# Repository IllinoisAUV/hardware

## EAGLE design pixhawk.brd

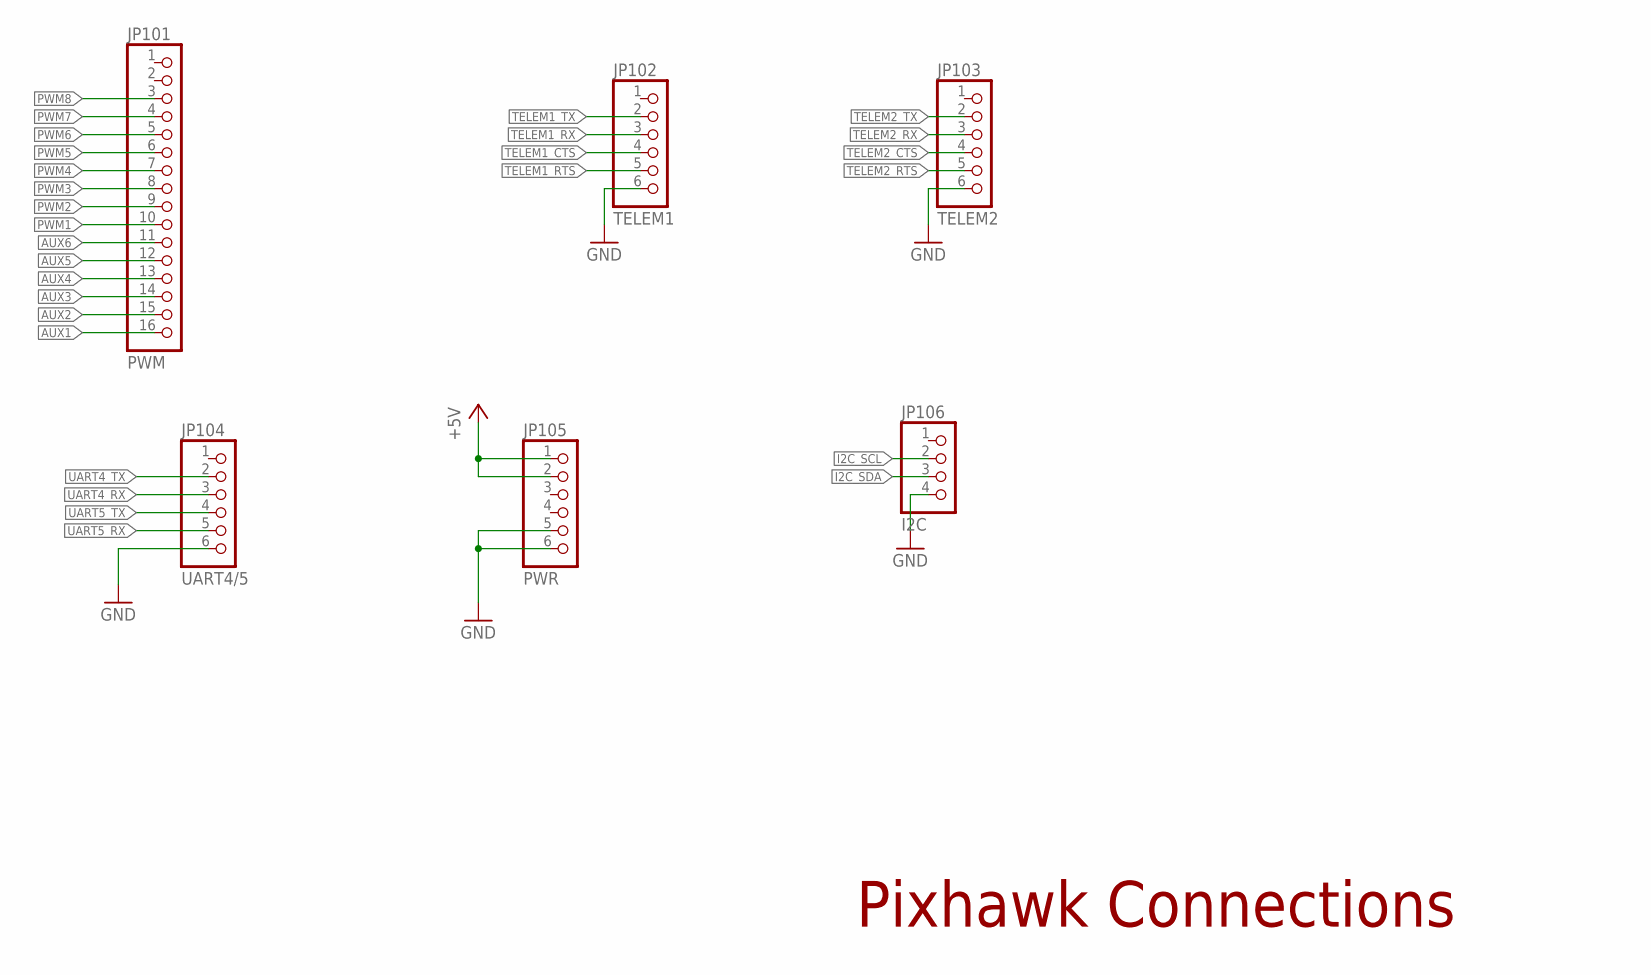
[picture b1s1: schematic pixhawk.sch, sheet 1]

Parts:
JP101: PWM; 1X16
JP102: TELEM1; 1X06
JP103: TELEM2; 1X06
JP104: UART4/5; 1X06
JP105: PWR; 1X06
JP106: I2C; 1X04

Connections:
+5V: JP105.1, JP105.2; also elsewhere on the board
AUX1: JP101.16; also elsewhere on the board
AUX2: JP101.15; also elsewhere on the board
AUX3: JP101.14; also elsewhere on the board
AUX4: JP101.13; also elsewhere on the board
AUX5: JP101.12; also elsewhere on the board
AUX6: JP101.11; also elsewhere on the board
GND: JP102.6, JP103.6, JP104.6, JP105.5, JP105.6, JP106.4; also elsewhere on the board
I2C_SCL: JP106.2; also elsewhere on the board
I2C_SDA: JP106.3; also elsewhere on the board
PWM1: JP101.10; also elsewhere on the board
PWM2: JP101.9; also elsewhere on the board
PWM3: JP101.8; also elsewhere on the board
PWM4: JP101.7; also elsewhere on the board
PWM5: JP101.6; also elsewhere on the board
PWM6: JP101.5; also elsewhere on the board
PWM7: JP101.4; also elsewhere on the board
PWM8: JP101.3; also elsewhere on the board
TELEM1_CTS: JP102.4
TELEM1_RTS: JP102.5
TELEM1_RX: JP102.3; also elsewhere on the board
TELEM1_TX: JP102.2; also elsewhere on the board
TELEM2_CTS: JP103.4
TELEM2_RTS: JP103.5
TELEM2_RX: JP103.3; also elsewhere on the board
TELEM2_TX: JP103.2; also elsewhere on the board
UART4_RX: JP104.3; also elsewhere on the board
UART4_TX: JP104.2; also elsewhere on the board
UART5_RX: JP104.5; also elsewhere on the board
UART5_TX: JP104.4; also elsewhere on the board

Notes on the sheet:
Pixhawk Connections

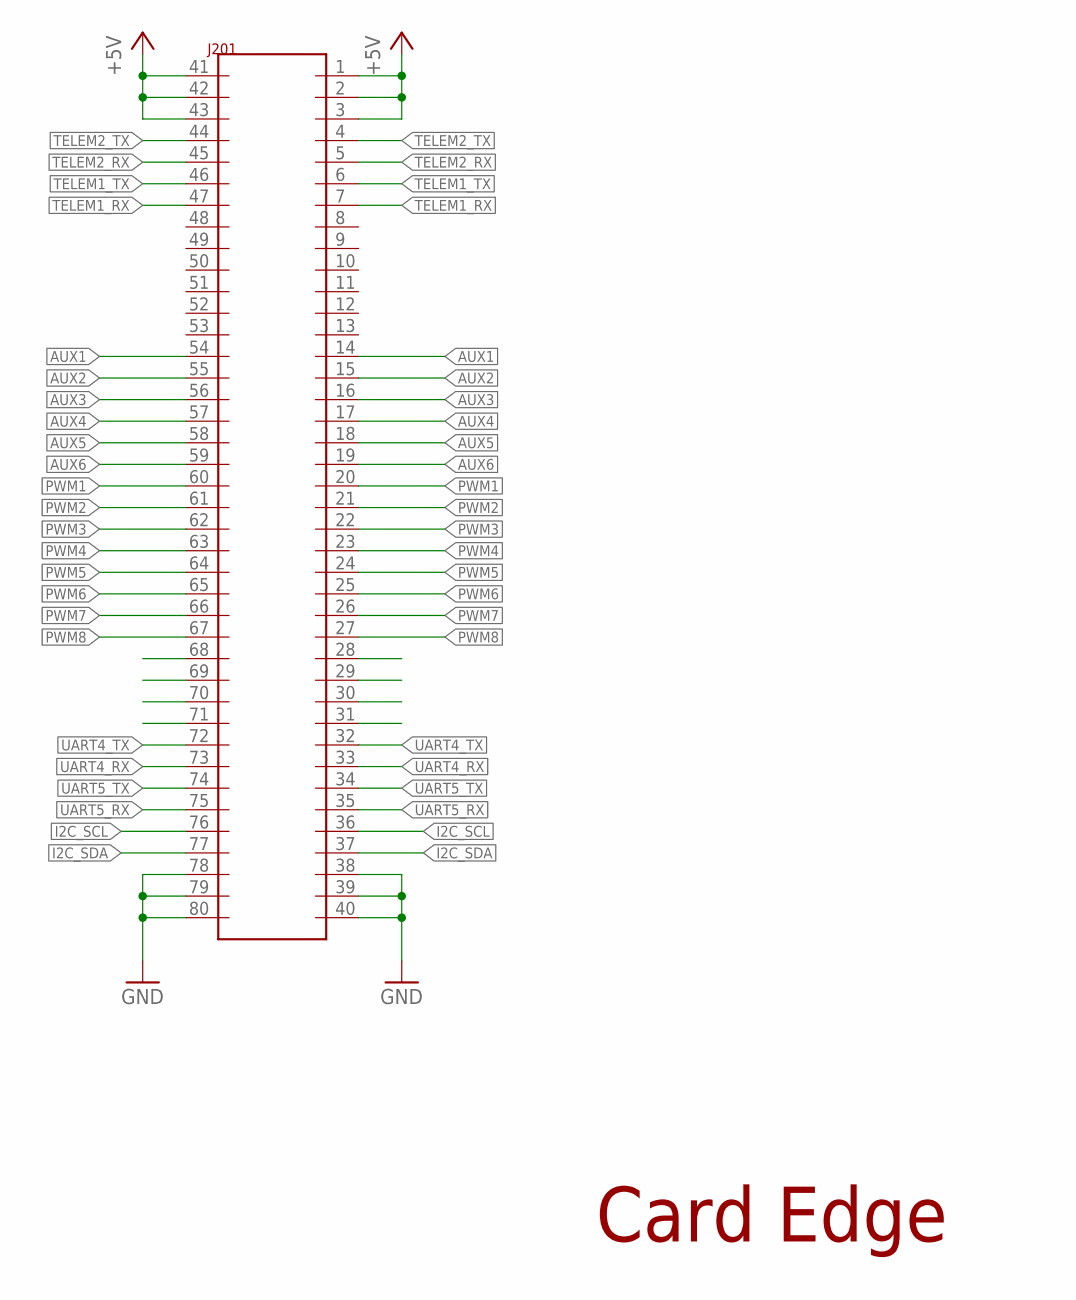
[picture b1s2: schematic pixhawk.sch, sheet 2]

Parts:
J201: 80-PIN-CARD-EDGE

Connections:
+5V: J201.1, J201.2, J201.3, J201.41, J201.42, J201.43; also elsewhere on the board
AUX1: J201.14, J201.54; also elsewhere on the board
AUX2: J201.15, J201.55; also elsewhere on the board
AUX3: J201.16, J201.56; also elsewhere on the board
AUX4: J201.17, J201.57; also elsewhere on the board
AUX5: J201.18, J201.58; also elsewhere on the board
AUX6: J201.19, J201.59; also elsewhere on the board
CAN_H: J201.30, J201.70
CAN_L: J201.31, J201.71
GND: J201.38, J201.39, J201.40, J201.78, J201.79, J201.80; also elsewhere on the board
I2C_SCL: J201.36, J201.76; also elsewhere on the board
I2C_SDA: J201.37, J201.77; also elsewhere on the board
PWM1: J201.20, J201.60; also elsewhere on the board
PWM2: J201.21, J201.61; also elsewhere on the board
PWM3: J201.22, J201.62; also elsewhere on the board
PWM4: J201.23, J201.63; also elsewhere on the board
PWM5: J201.24, J201.64; also elsewhere on the board
PWM6: J201.25, J201.65; also elsewhere on the board
PWM7: J201.26, J201.66; also elsewhere on the board
PWM8: J201.27, J201.67; also elsewhere on the board
TELEM1_RX: J201.7, J201.47; also elsewhere on the board
TELEM1_TX: J201.6, J201.46; also elsewhere on the board
TELEM2_RX: J201.5, J201.45; also elsewhere on the board
TELEM2_TX: J201.4, J201.44; also elsewhere on the board
UART4_RX: J201.33, J201.73; also elsewhere on the board
UART4_TX: J201.32, J201.72; also elsewhere on the board
UART5_RX: J201.35, J201.75; also elsewhere on the board
UART5_TX: J201.34, J201.74; also elsewhere on the board

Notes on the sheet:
Card Edge

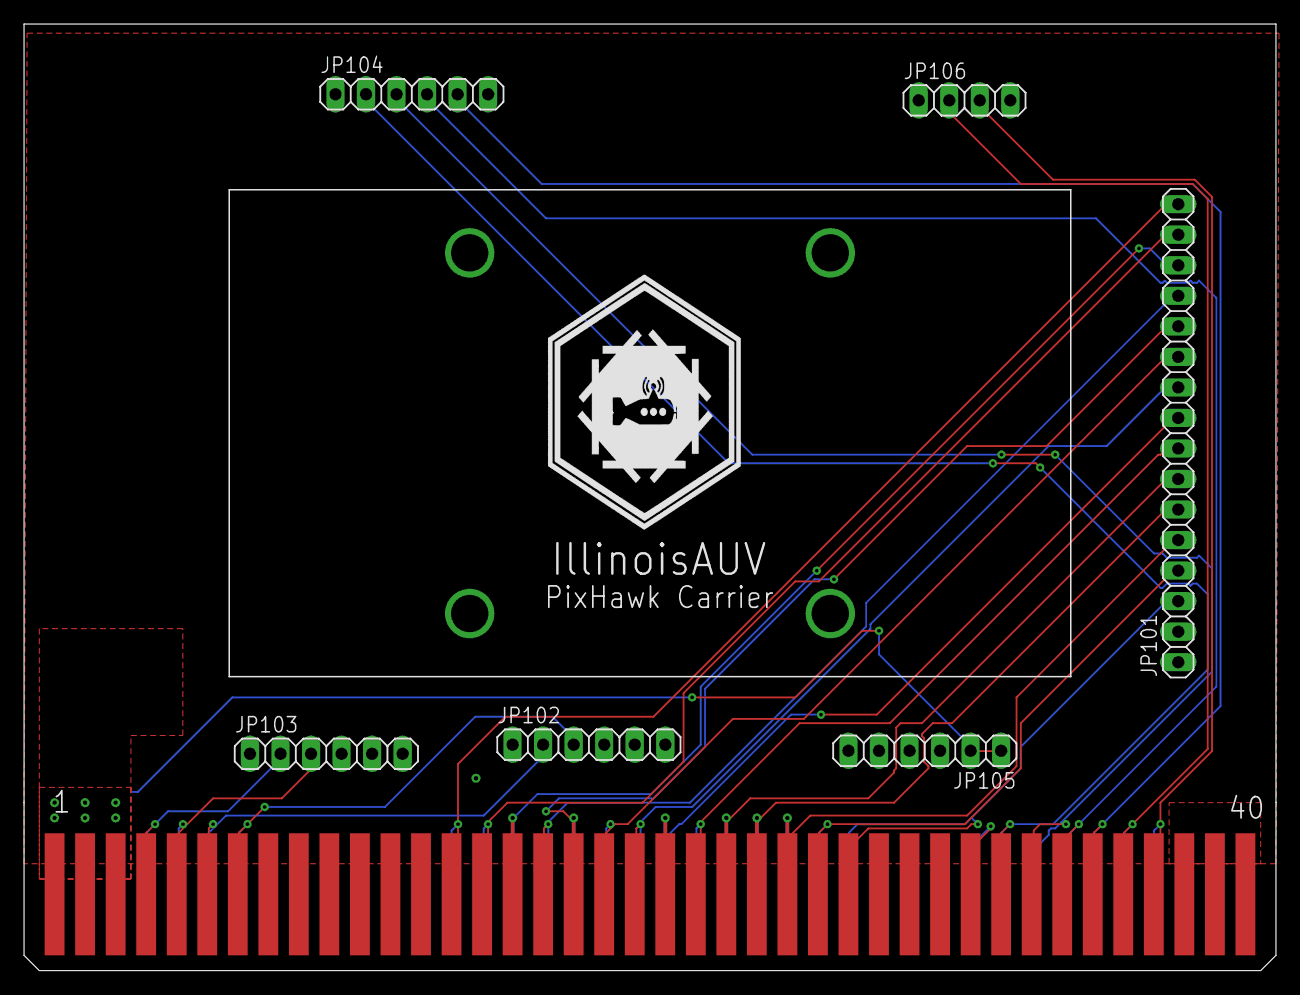
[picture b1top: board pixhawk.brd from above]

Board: 2 copper layers, 104.1 x 78.7 mm, 9 parts (0 on the bottom side), 28 nets.

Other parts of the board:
U$1: PIXHAWK_MOUNTING_HOLES
U$2: ILLINOISAUV

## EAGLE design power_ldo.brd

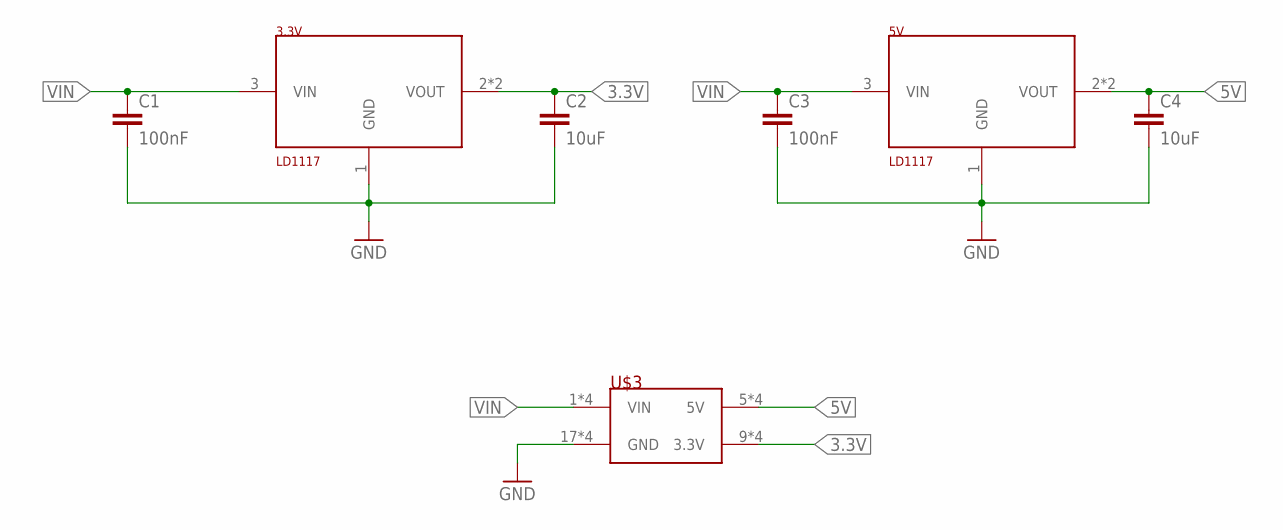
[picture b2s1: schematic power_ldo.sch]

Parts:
3.3V, 5V: LD1117"; SOT223
C1, C3: 100nF; C0603
C2, C4: 10uF; C0603
U$3: POWER_EDGE_CONNEDGE; 20-PIN-CARD-EDGE

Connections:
3.3V: 3.3V.2 (VOUT), 3.3V.4 (VOUT), C2.1, U$3.9 (3.3V), U$3.10 (3.3V), U$3.11 (3.3V), U$3.12 (3.3V)
5V: 5V.2 (VOUT), 5V.4 (VOUT), C4.1, U$3.5 (5V), U$3.6 (5V), U$3.7 (5V), U$3.8 (5V)
GND: 3.3V.1 (GND), 5V.1 (GND), C1.2, C2.2, C3.2, C4.2, U$3.17 (GND), U$3.18 (GND), U$3.19 (GND), U$3.20 (GND)
VIN: 3.3V.3 (VIN), 5V.3 (VIN), C1.1, C3.1, U$3.1 (VIN), U$3.2 (VIN), U$3.3 (VIN), U$3.4 (VIN)

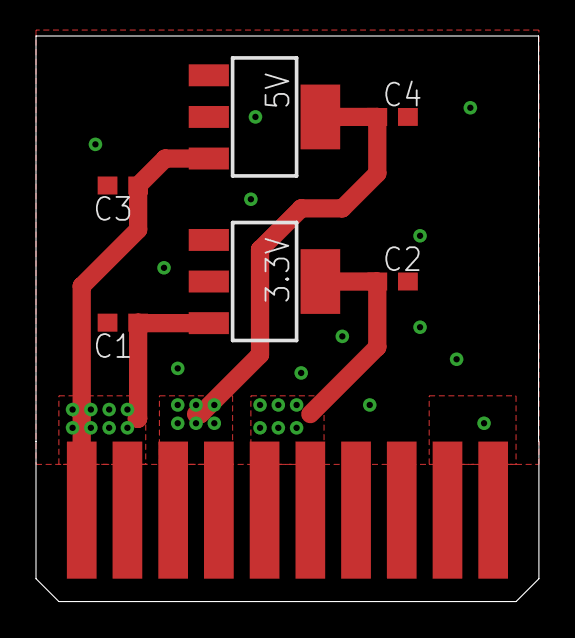
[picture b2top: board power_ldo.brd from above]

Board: 2 copper layers, 27.9 x 31.4 mm, 8 parts (1 on the bottom side), 4 nets.

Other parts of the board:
U$1: ILLINOISAUV

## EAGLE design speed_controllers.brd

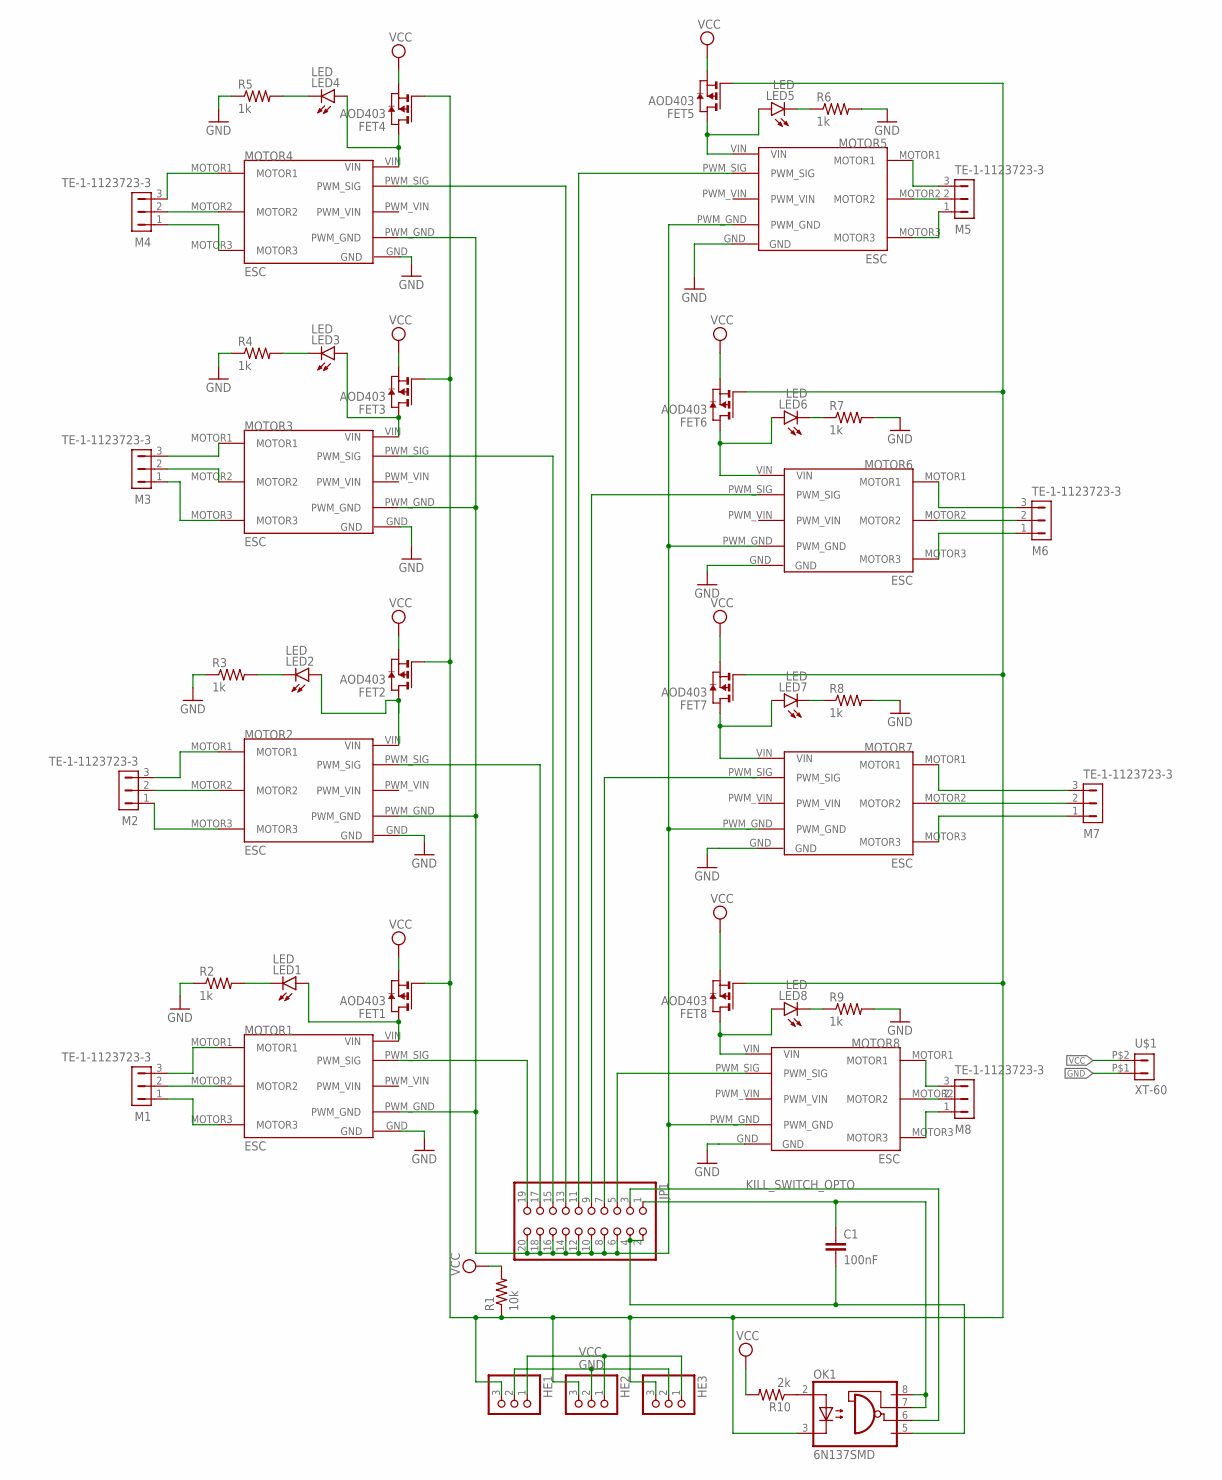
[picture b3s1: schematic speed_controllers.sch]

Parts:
C1: 100nF; C0603
FET1, FET2, FET3, FET4, FET5, FET6, FET7, FET8: AOD403; TO252
HE1, HE2, HE3: PINHD-1X3; 1X03
JP1: PINHD-2X10; 2X10
LED1, LED2, LED3, LED4, LED5, LED6, LED7, LED8: LED; LED-0603
M1, M2, M3, M4, M5, M6, M7, M8: TE-1-1123723-3
MOTOR1, MOTOR2, MOTOR3, MOTOR4, MOTOR5, MOTOR6, MOTOR7, MOTOR8: ESC
OK1: 6N137SMD; DIL8-SMD
R1: 10k; R0603
R2, R3, R4, R5, R6, R7, R8, R9: 1k; R0603
R10: 2k; R0603
U$1: XT-60

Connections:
FET_G: FET1.G, FET2.G, FET3.G, FET4.G, FET5.G, FET6.G, FET7.G, FET8.G, HE1.3, HE2.3, HE3.3, OK1.3 (C), R1.1
GND: HE1.2, HE2.2, HE3.2, MOTOR1.GND, MOTOR2.GND, MOTOR3.GND, MOTOR4.GND, MOTOR5.GND, MOTOR6.GND, MOTOR7.GND, MOTOR8.GND, R2.1, R3.1, R4.1, R5.1, R6.2, R7.2, R8.2, R9.2, U$1.P$1 (2)
KILL_SWITCH_OPTO: JP1.3, OK1.6 (VO)
M1_1: M1.1, MOTOR1.MOTOR3
M1_2: M1.2, MOTOR1.MOTOR2
M1_3: M1.3, MOTOR1.MOTOR1
M2_1: M2.1, MOTOR2.MOTOR3
M2_2: M2.2, MOTOR2.MOTOR2
M2_3: M2.3, MOTOR2.MOTOR1
M3_1: M3.1, MOTOR3.MOTOR3
M3_2: M3.2, MOTOR3.MOTOR2
M3_3: M3.3, MOTOR3.MOTOR1
M4_1: M4.1, MOTOR4.MOTOR3
M4_2: M4.2, MOTOR4.MOTOR2
M4_3: M4.3, MOTOR4.MOTOR1
M5_1: M5.1, MOTOR5.MOTOR3
M5_2: M5.2, MOTOR5.MOTOR2
M5_3: M5.3, MOTOR5.MOTOR1
M6_1: M6.1, MOTOR6.MOTOR3
M6_2: M6.2, MOTOR6.MOTOR2
M6_3: M6.3, MOTOR6.MOTOR1
M7_1: M7.1, MOTOR7.MOTOR3
M7_2: M7.2, MOTOR7.MOTOR2
M7_3: M7.3, MOTOR7.MOTOR1
M8_1: M8.1, MOTOR8.MOTOR3
M8_2: M8.2, MOTOR8.MOTOR2
M8_3: M8.3, MOTOR8.MOTOR1
MCU_GND: C1.2, JP1.2, JP1.4, OK1.5 (GND)
MCU_VCC: C1.1, JP1.1, OK1.7 (VE), OK1.8 (VCC)
unnamed: OK1.2 (A), R10.1
unnamed: LED1.C, R2.2
unnamed: LED2.C, R3.2
unnamed: LED3.C, R4.2
unnamed: LED4.C, R5.2
unnamed: LED5.C, R6.1
unnamed: LED7.C, R8.1
unnamed: LED8.C, R9.1
PWM_GND: JP1.6, JP1.8, JP1.10, JP1.12, JP1.14, JP1.16, JP1.18, JP1.20, MOTOR1.PWM_GND, MOTOR2.PWM_GND, MOTOR3.PWM_GND, MOTOR4.PWM_GND, MOTOR5.PWM_GND, MOTOR6.PWM_GND, MOTOR7.PWM_GND, MOTOR8.PWM_GND
R7: LED6.C, R7.1
SIG_1: JP1.19, MOTOR1.PWM_SIG
SIG_2: JP1.17, MOTOR2.PWM_SIG
SIG_3: JP1.15, MOTOR3.PWM_SIG
SIG_4: JP1.13, MOTOR4.PWM_SIG
SIG_5: JP1.11, MOTOR5.PWM_SIG
SIG_6: JP1.9, MOTOR6.PWM_SIG
SIG_7: JP1.7, MOTOR7.PWM_SIG
SIG_8: JP1.5, MOTOR8.PWM_SIG
VCC: FET1.S, FET2.S, HE1.1, HE2.1, HE3.1, R1.2, R10.2, U$1.P$2 (1)
VIN3: FET3.D, LED3.A, MOTOR3.VIN
VIN_1: FET1.D, LED1.A, MOTOR1.VIN
VIN_2: FET2.D, LED2.A, MOTOR2.VIN
VIN_4: FET4.D, LED4.A, MOTOR4.VIN
VIN_5: FET5.D, LED5.A, MOTOR5.VIN
VIN_6: FET6.D, LED6.A, MOTOR6.VIN
VIN_7: FET7.D, LED7.A, MOTOR7.VIN
VIN_8: FET8.D, LED8.A, MOTOR8.VIN

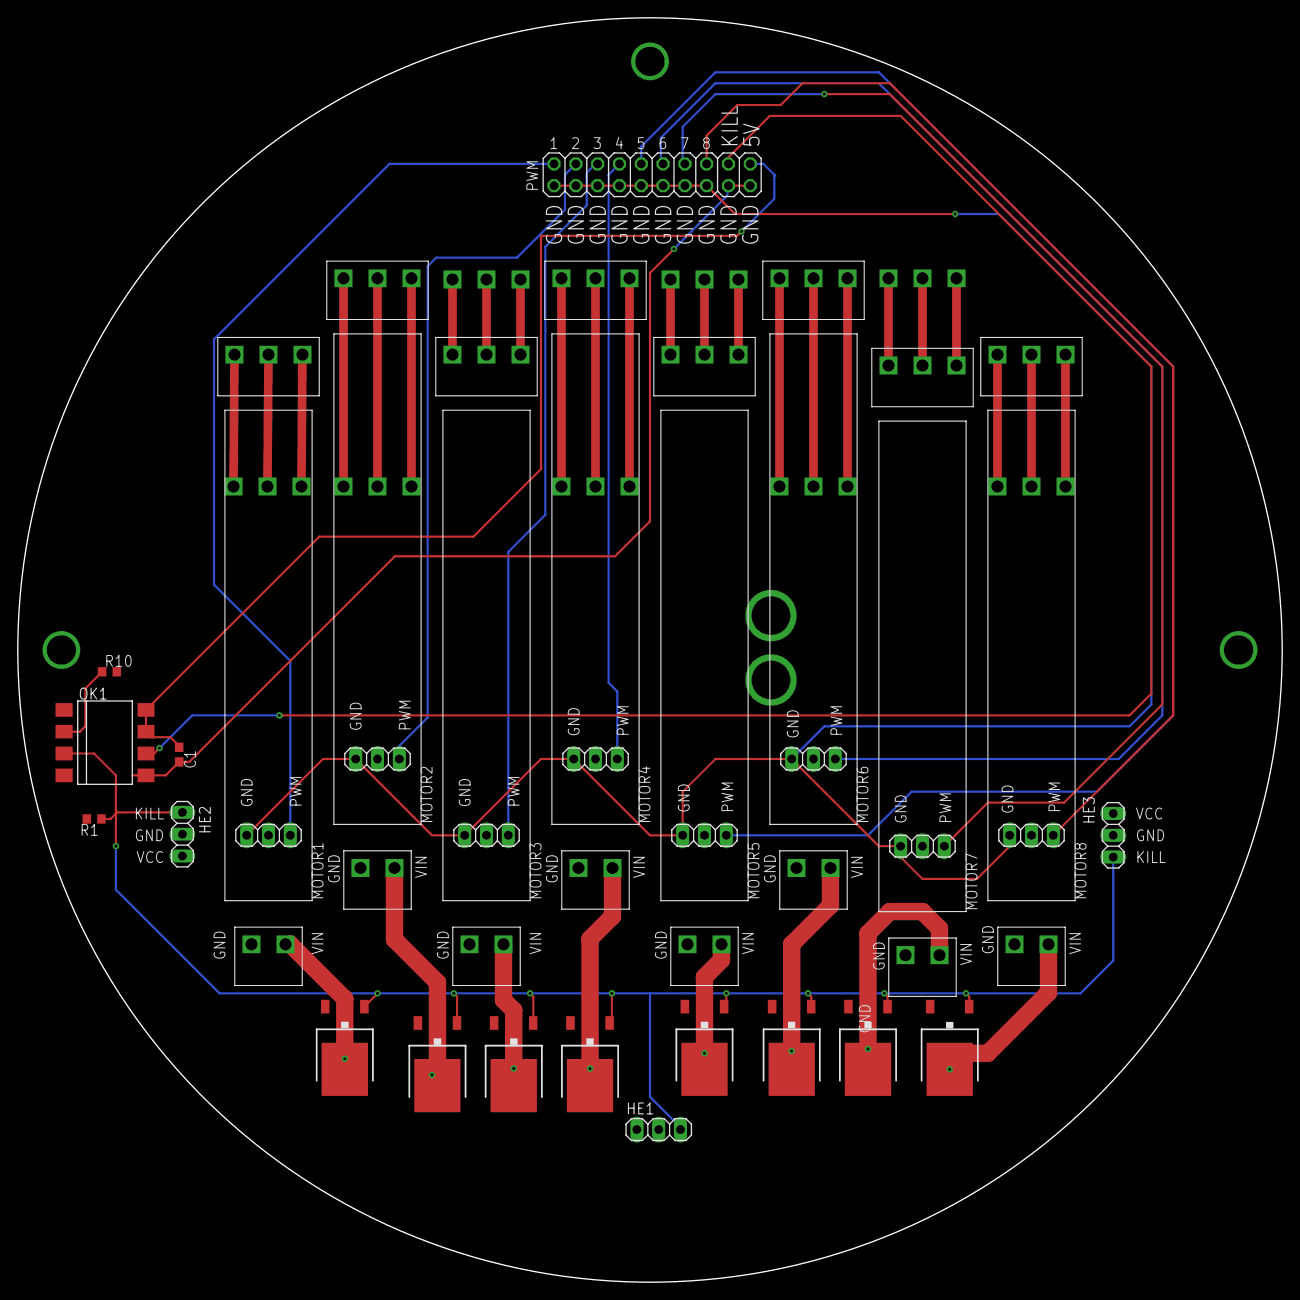
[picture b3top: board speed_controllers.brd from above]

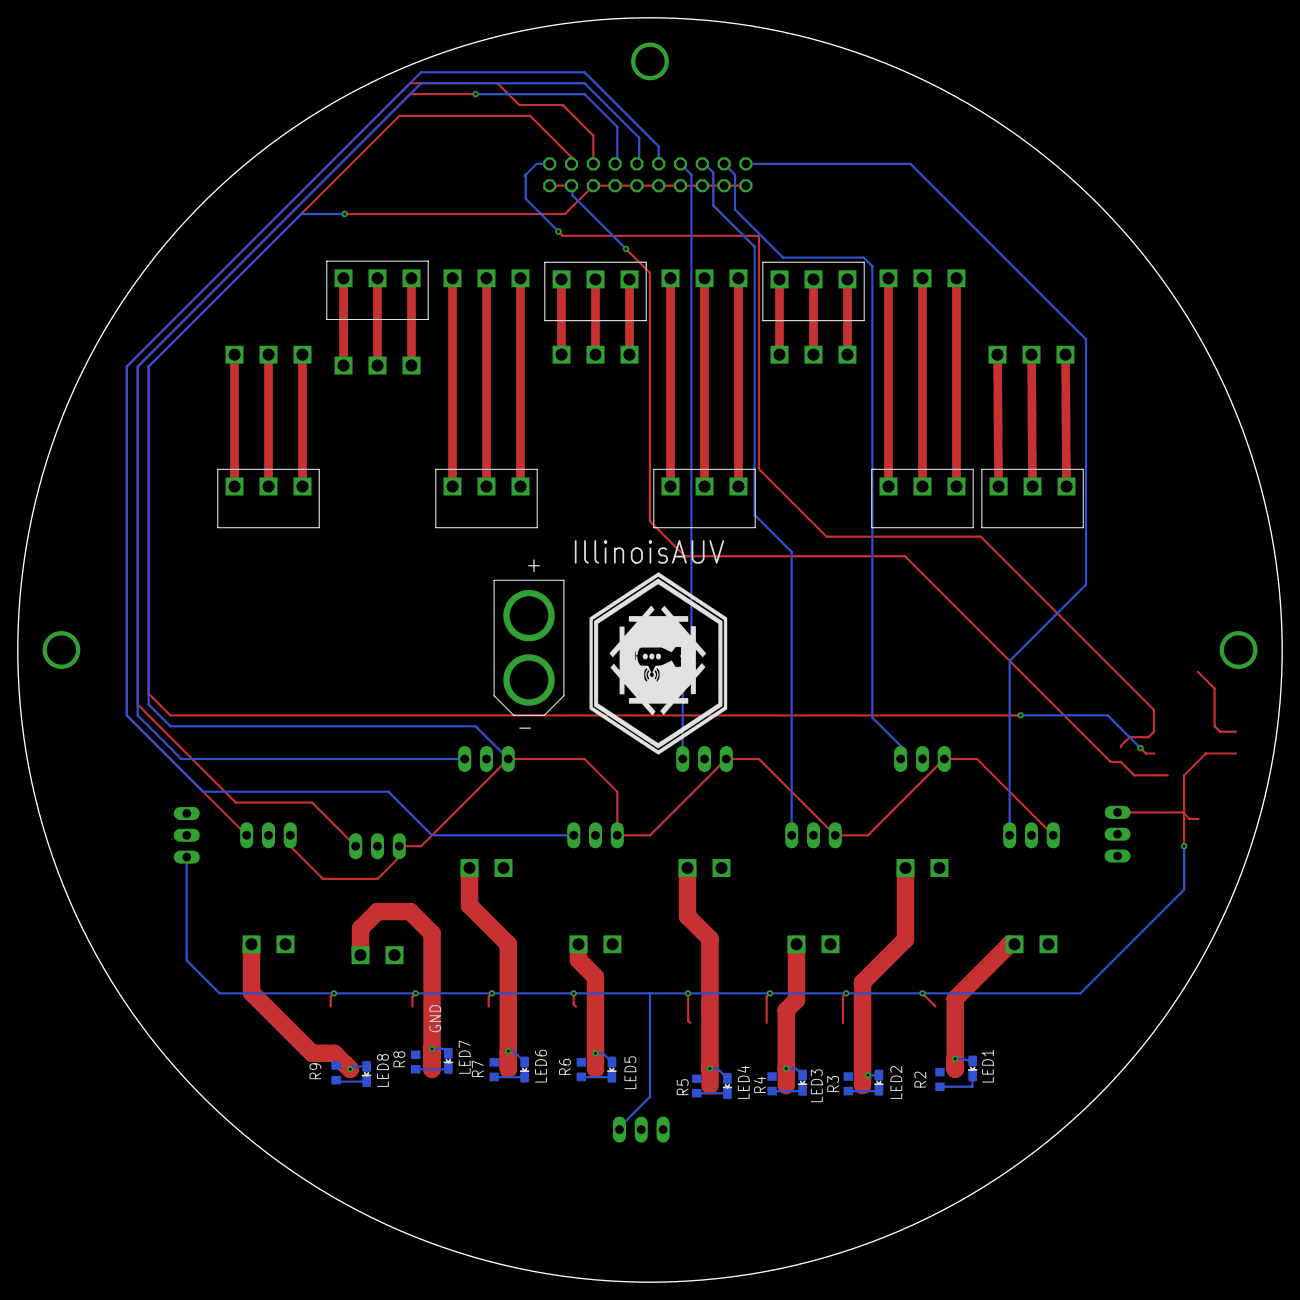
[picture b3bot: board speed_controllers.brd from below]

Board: 2 copper layers, 147.3 x 147.3 mm, 50 parts (26 on the bottom side), 56 nets.

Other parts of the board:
U$2: ILLINOISAUV

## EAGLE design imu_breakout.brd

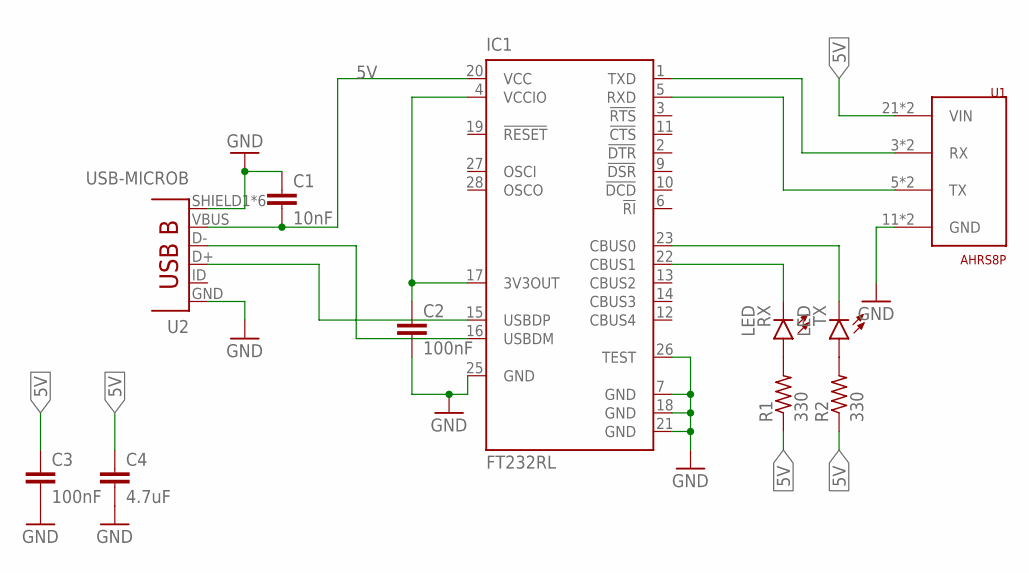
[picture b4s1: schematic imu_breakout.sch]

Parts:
C1: 10nF; C0603
C2, C3: 100nF; C0603
C4: 4.7uF; C0603
IC1: FT232RL; SSOP28
R1, R2: 330; R0603
RX: LED; LED-0603
TX: LED; LED-0603
U1: AHRS8P_CONN; ST4-10-1.00-L-D-P-TR
U2: USB-MICROB; USB-B-MICRO-SMD

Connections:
3V3OUT: C2.1, IC1.4 (VCCIO), IC1.17 (3V3OUT)
5V: C1.2, C3.1, C4.1, IC1.20 (VCC), R1.1, R2.1, U1.21 (VIN), U1.22 (VIN), U2.VBUS
GND: C1.1, C2.2, C3.2, C4.2, IC1.7 (GND), IC1.18 (GND), IC1.21 (GND), IC1.25 (GND), IC1.26 (TEST), U1.11 (GND), U1.12 (GND), U2.GND, U2.SHIELD1 (SHIELD), U2.SHIELD2 (SHIELD), U2.SHIELD3 (SHIELD), U2.SHIELD4 (SHIELD), U2.SHIELD5 (SHIELD), U2.SHIELD6 (SHIELD)
IMU_RX: IC1.1 (TXD), U1.3 (RX), U1.4 (RX)
IMU_TX: IC1.5 (RXD), U1.5 (TX), U1.6 (TX)
unnamed: R1.2, RX.A
unnamed: R2.2, TX.A
RX_LED: IC1.22 (CBUS1), RX.C
TX_LED: IC1.23 (CBUS0), TX.C
USBDM: IC1.16 (USBDM), U2.D-
USBDP: IC1.15 (USBDP), U2.D+

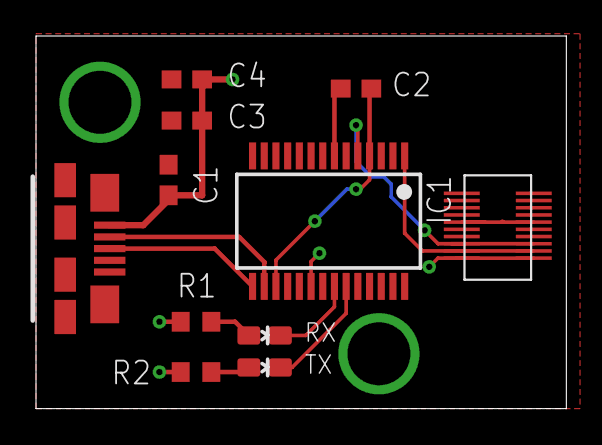
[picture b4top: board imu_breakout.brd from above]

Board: 2 copper layers, 29.5 x 20.7 mm, 12 parts (1 on the bottom side), 11 nets.

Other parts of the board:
U$1: ILLINOISAUV

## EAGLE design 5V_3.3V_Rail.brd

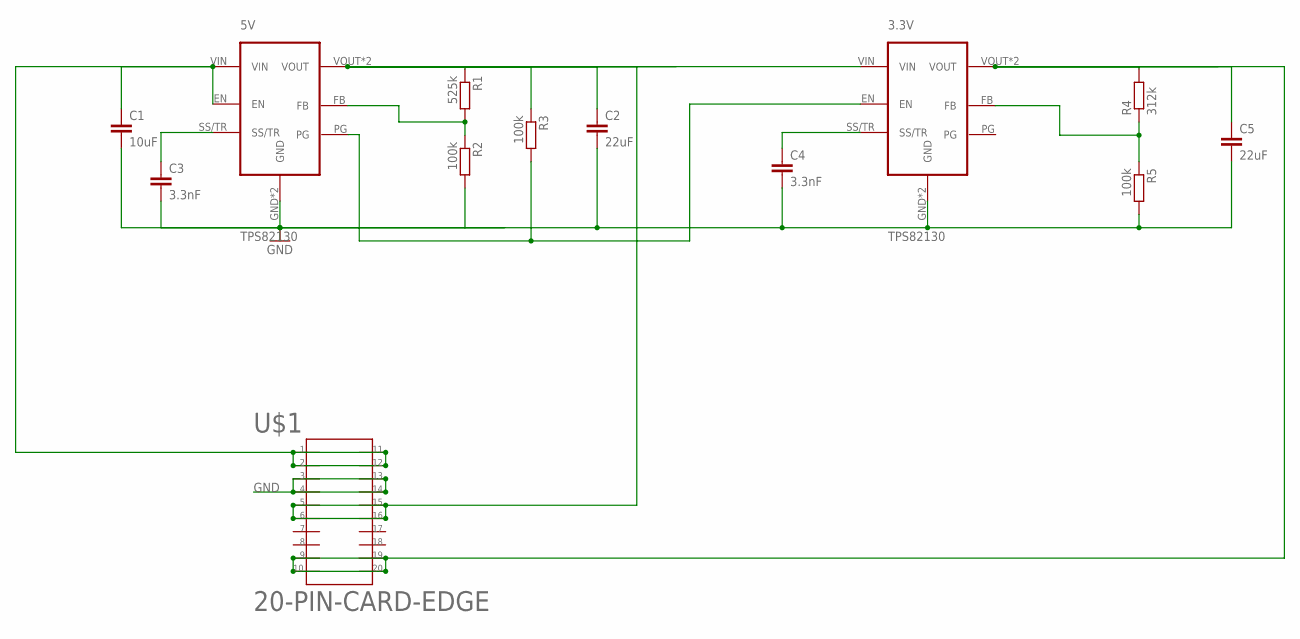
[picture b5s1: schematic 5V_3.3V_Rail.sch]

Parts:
3.3V, 5V: TPS82130
C1: 10uF; C0603
C2, C5: 22uF; C0603
C3, C4: 3.3nF; C0603
R1: 525k; R0603
R2, R3, R5: 100k; R0603
R4: 312k; R0603
U$1: 20-PIN-CARD-EDGE

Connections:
FB: 5V.FB, R1.2, R2.1
FB2: 3.3V.FB, R4.1, R5.1
GND: 3.3V.GND, 3.3V.GND_PAD (GND), 5V.GND, 5V.GND_PAD (GND), C1.2, C2.2, C3.2, C4.2, C5.2, R2.2, R5.2, U$1.P$3, U$1.P$4, U$1.P$13, U$1.P$14
PG: 3.3V.EN, 5V.PG, R3.2
SS2: 3.3V.SS/TR, C4.1
SS/TR: 5V.SS/TR, C3.1
VIN: 5V.EN, 5V.VIN, C1.1, U$1.P$1, U$1.P$2, U$1.P$11, U$1.P$12
VOUT1: 3.3V.VIN, 5V.VOUT, 5V.VOUT_2 (VOUT), C2.1, R1.1, R3.1, U$1.P$5, U$1.P$6, U$1.P$15, U$1.P$16
VOUT2: 3.3V.VOUT, 3.3V.VOUT_2 (VOUT), C5.1, R4.2, U$1.P$9, U$1.P$10, U$1.P$19, U$1.P$20

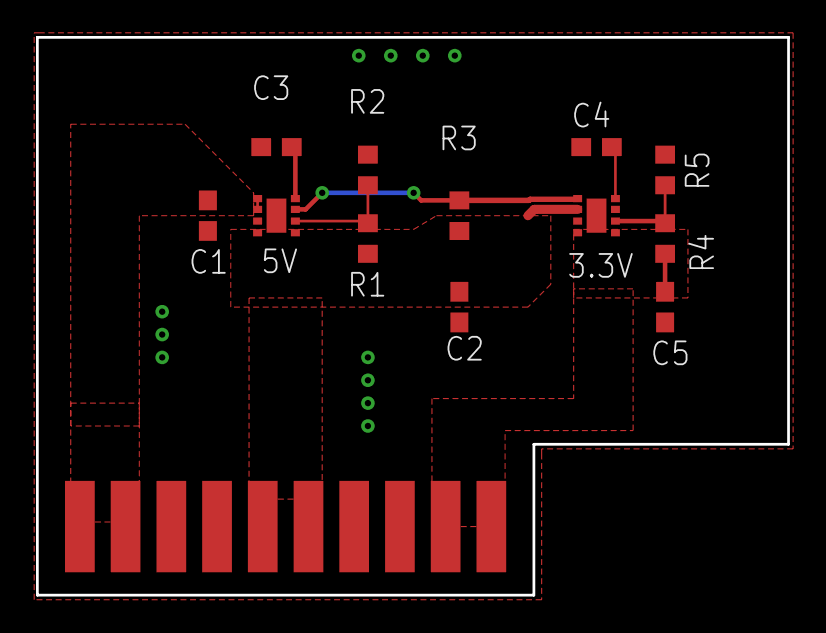
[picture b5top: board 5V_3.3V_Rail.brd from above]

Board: 2 copper layers, 41.7 x 31.0 mm, 13 parts (0 on the bottom side), 9 nets.

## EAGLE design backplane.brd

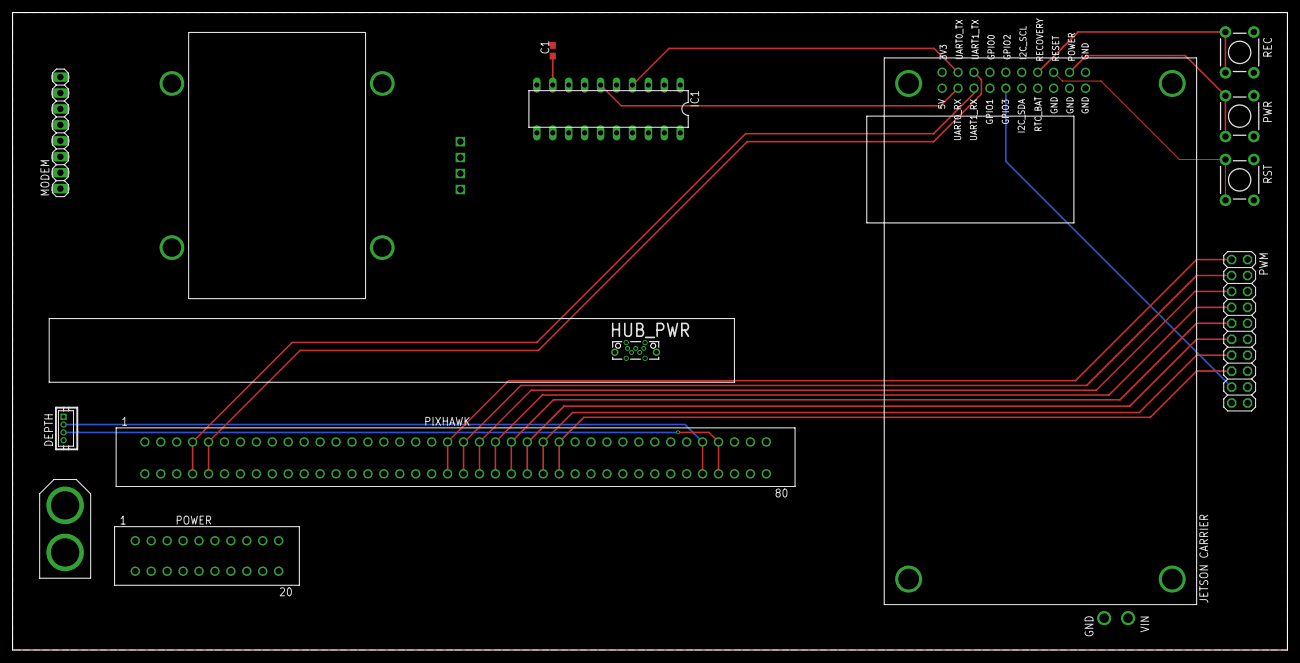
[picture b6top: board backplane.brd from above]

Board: 2 copper layers, 203.2 x 101.6 mm, 14 parts (0 on the bottom side), 23 nets.

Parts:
BAT: XT-60
C1: 0.1uF; C0603
DEPTH: DF13-4P-1.25DSA
HUB_PWR: USB3150-30-130-A; GCT_USB3150-XX-XXX-X_REVA
IC1: MAX3233ECPP; DIL20
MODEM: 1X08
PIXHAWK: PIXHAWK_EDGE_CONNCONN; TE-2-5530843-0
POWER: TE-5-5530843-0
PWM: 2X10
PWR: TACTILE-PTH
REC: TACTILE-PTH
RST: TACTILE-PTH
U$1: AHRS8P
U$3: ORBITTY_CARRIER

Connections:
+3V3: C1.1, IC1.9
+5V: HUB_PWR.1, PIXHAWK.1, PIXHAWK.2, PIXHAWK.3, PIXHAWK.4, PIXHAWK.5, PIXHAWK.6, U$1.VIN
GND: BAT.P$2, C1.2, DEPTH.P$4, HUB_PWR.5, HUB_PWR.6, HUB_PWR.7, HUB_PWR.8, HUB_PWR.9, HUB_PWR.10, HUB_PWR.11, IC1.18, PIXHAWK.75, PIXHAWK.76, PIXHAWK.77, PIXHAWK.78, PIXHAWK.79, PIXHAWK.80, PWM.2, PWM.4, PWM.6, PWM.8, PWM.10, PWM.12, PWM.14, PWM.16, PWM.18, PWM.20, REC.1, REC.2, RST.1, RST.2, U$1.GND, U$3.GND, U$3.GND1, U$3.GND2, U$3.GND3, U$3.GND4
MODEM_RX: IC1.4, U$3.UART0_TX
MODEM_TX: IC1.6, U$3.UART0_RX
unnamed: PWR.3, PWR.4, U$3.POWER_BUTTON
unnamed: RST.3, RST.4, U$3.RESET
unnamed: REC.3, REC.4, U$3.RECOVERY
PIXHAWK_GPIO3: PWM.17, U$3.GPIO3
PIXHAWK_I2C_SCL: DEPTH.P$2, PIXHAWK.71, PIXHAWK.72
PIXHAWK_I2C_SDA: DEPTH.P$3, PIXHAWK.73, PIXHAWK.74
PIXHAWK_TELEM2_RX: PIXHAWK.9, PIXHAWK.10, U$3.UART1_TX
PIXHAWK_TELEM2_TX: PIXHAWK.7, PIXHAWK.8, U$3.UART1_RX
PWM1: PIXHAWK.39, PIXHAWK.40, PWM.1
PWM2: PIXHAWK.41, PIXHAWK.42, PWM.3
PWM3: PIXHAWK.43, PIXHAWK.44, PWM.5
PWM4: PIXHAWK.45, PIXHAWK.46, PWM.7
PWM5: PIXHAWK.47, PIXHAWK.48, PWM.9
PWM6: PIXHAWK.49, PIXHAWK.50, PWM.11
PWM7: PIXHAWK.51, PIXHAWK.52, PWM.13
PWM8: PIXHAWK.53, PIXHAWK.54, PWM.15
PWR: PWR.1, PWR.2
VBAT: BAT.P$1, U$3.VIN

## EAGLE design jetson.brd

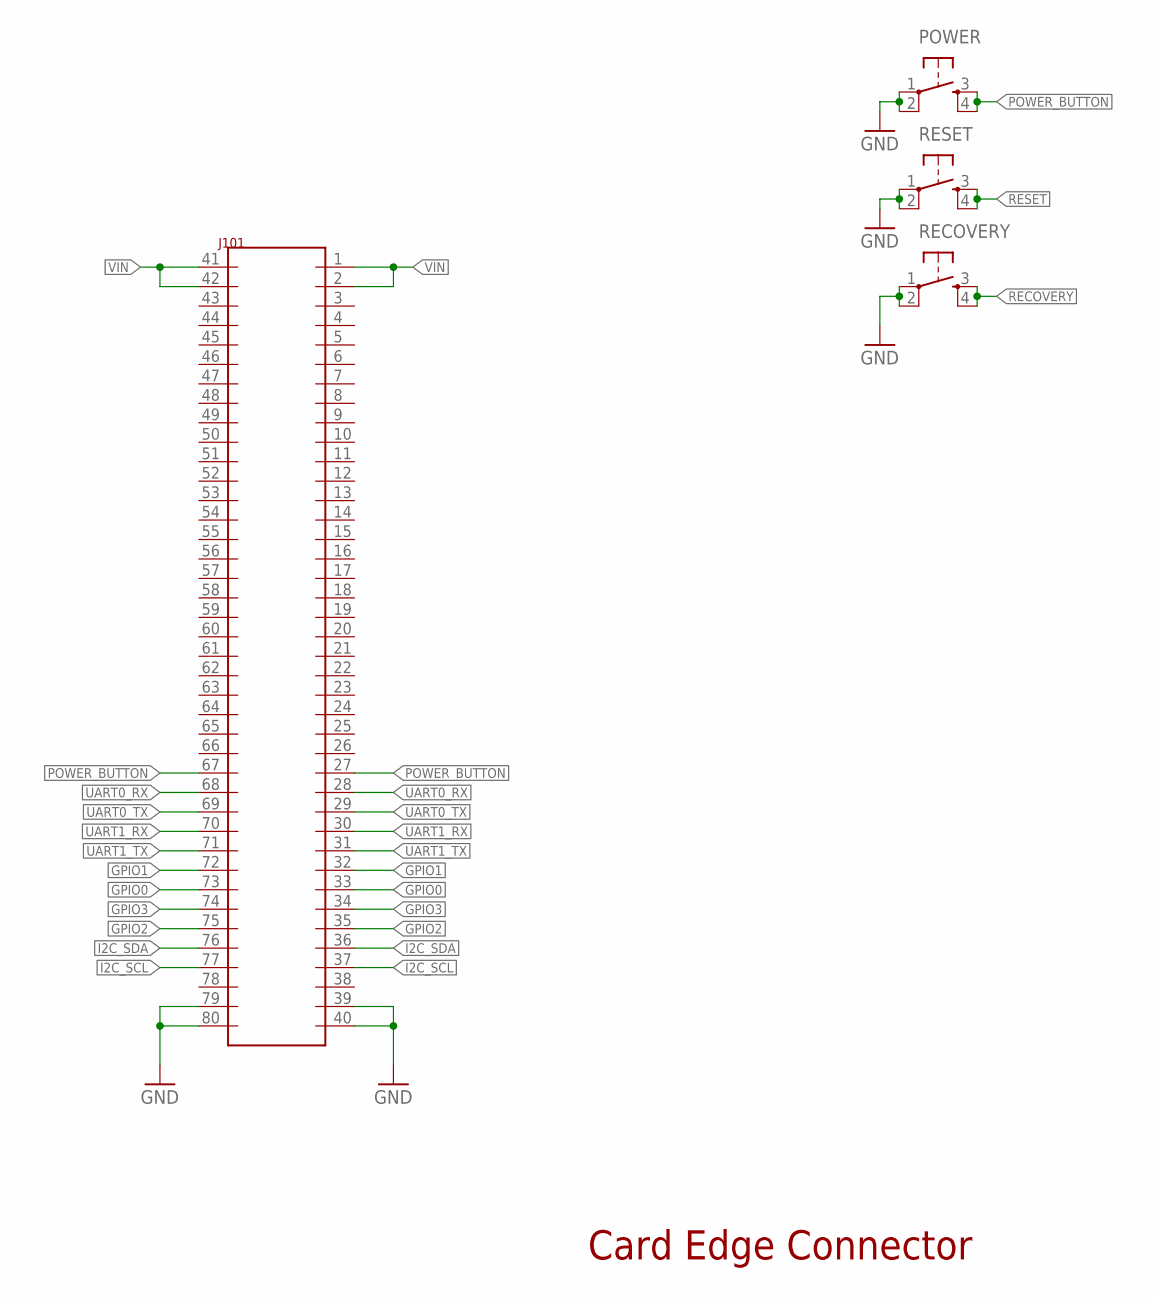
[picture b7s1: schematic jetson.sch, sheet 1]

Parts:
J101: 80-PIN-CARD-EDGE
POWER: TAC_SWITCHPTH; TACTILE-PTH
RECOVERY: TAC_SWITCHPTH; TACTILE-PTH
RESET: TAC_SWITCHPTH; TACTILE-PTH

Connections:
GND: J101.39, J101.40, J101.79, J101.80, POWER.1, POWER.2, RECOVERY.1, RECOVERY.2, RESET.1, RESET.2; also elsewhere on the board
GPIO0: J101.33, J101.73; also elsewhere on the board
GPIO1: J101.32, J101.72; also elsewhere on the board
GPIO2: J101.35, J101.75; also elsewhere on the board
GPIO3: J101.34, J101.74; also elsewhere on the board
I2C_SCL: J101.37, J101.77; also elsewhere on the board
I2C_SDA: J101.36, J101.76; also elsewhere on the board
POWER_BUTTON: J101.27, J101.67, POWER.3, POWER.4; also elsewhere on the board
RECOVERY: RECOVERY.3, RECOVERY.4; also elsewhere on the board
RESET: RESET.3, RESET.4; also elsewhere on the board
UART0_RX: J101.28, J101.68; also elsewhere on the board
UART0_TX: J101.29, J101.69; also elsewhere on the board
UART1_RX: J101.30, J101.70; also elsewhere on the board
UART1_TX: J101.31, J101.71; also elsewhere on the board
VIN: J101.1, J101.2, J101.41, J101.42; also elsewhere on the board

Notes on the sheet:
Card Edge Connector
